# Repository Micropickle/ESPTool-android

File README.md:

# ESPTool-android
an extension to your phone meant to provide extended RF capabilities

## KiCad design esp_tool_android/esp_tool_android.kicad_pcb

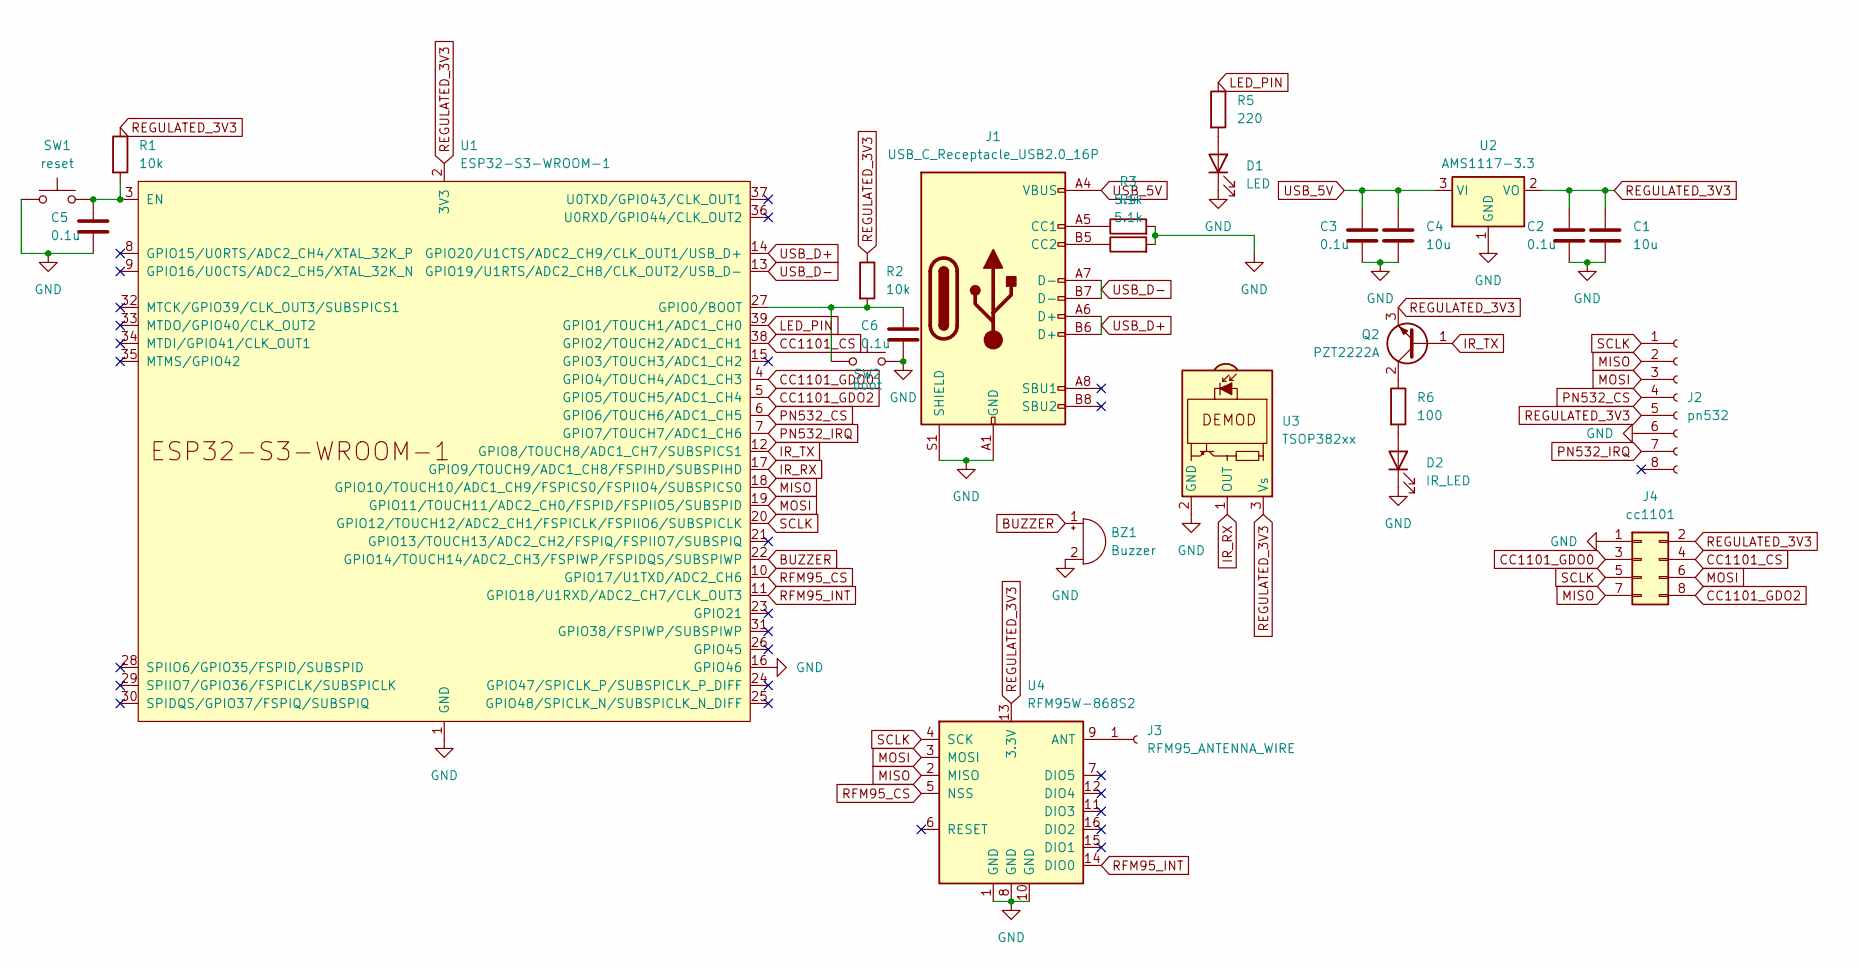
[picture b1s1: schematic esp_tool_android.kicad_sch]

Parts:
BZ1: Buzzer; PinHeader_1x02_P2.54mm_Vertical
C1, C4: 10u; C_0805_2012Metric
C2, C3, C5, C6: 0.1u; C_0805_2012Metric
D1: LED; LED_0805_2012Metric
D2: IR_LED; LED_D3.0mm_Horizontal_O1.27mm_Z2.0mm_Clear
J1: USB_C_Receptacle_USB2.0_16P; USB_C_Receptacle_HRO_TYPE-C-31-M-12
J2: pn532; PinHeader_1x08_P2.54mm_Vertical
J3: RFM95_ANTENNA_WIRE; PinHeader_1x01_P2.54mm_Vertical
J4: cc1101; PinHeader_2x04_P2.54mm_Vertical
Q2: PZT2222A; SOT-223-3_TabPin2
R1, R2: 10k; R_0805_2012Metric
R3, R4: 5.1k; R_0805_2012Metric
R5: 220; R_0805_2012Metric
R6: 100; R_0805_2012Metric
SW1: reset; SW_PUSH_6mm_H5mm
SW2: boot; SW_PUSH_6mm_H5mm
U1: ESP32-S3-WROOM-1
U2: AMS1117-3.3; SOT-223-3_TabPin2
U3: TSOP382xx; Vishay_MINICAST-3Pin
U4: RFM95W-868S2; HOPERF_RFM9XW_SMD

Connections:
BUZZER: BZ1.1 (+), U1.22 (GPIO14/TOUCH14/ADC2_CH3/FSPIWP/FSPIDQS/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)
CC1101_CS: J4.4, U1.38 (GPIO2/TOUCH2/ADC1_CH1)
CC1101_GDO0: J4.3, U1.4 (GPIO4/TOUCH4/ADC1_CH3)
CC1101_GDO2: J4.8, U1.5 (GPIO5/TOUCH5/ADC1_CH4)
GND: BZ1.2 (-), C1.2, C2.2, C3.2, C4.2, C5.2, C6.2, D1.1 (K), D2.1 (K), J1.A1 (GND), J1.A12 (GND), J1.B1 (GND), J1.B12 (GND), J1.S1 (SHIELD), J2.6, J4.1, R3.2, R4.2, SW1.1, SW2.2, U1.1 (GND), U1.16 (GPIO46), U1.40 (GND), U1.41 (GND), U2.1 (GND), U3.2 (GND), U4.1 (GND), U4.8 (GND), U4.10 (GND)
IR_RX: U1.17 (GPIO9/TOUCH9/ADC1_CH8/FSPIHD/SUBSPIHD), U3.1 (OUT)
IR_TX: Q2.1 (B), U1.12 (GPIO8/TOUCH8/ADC1_CH7/SUBSPICS1)
LED_PIN: R5.1, U1.39 (GPIO1/TOUCH1/ADC1_CH0)
MISO: J2.2, J4.7, U1.18 (GPIO10/TOUCH10/ADC1_CH9/FSPICS0/FSPIIO4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), U4.2 (MISO)
MOSI: J2.3, J4.6, U1.19 (GPIO11/TOUCH11/ADC2_CH0/FSPID/FSPIIO5/S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), U4.3 (MOSI)
unnamed: D1.2 (A), R5.2
unnamed: D2.2 (A), R6.2
unnamed: J1.A5 (CC1), R3.1
unnamed: J1.B5 (CC2), R4.1
unnamed: J3.1, U4.9 (ANT)
unnamed: Q2.2 (C), R6.1
unnamed: C5.1, R1.2, SW1.2, U1.3 (EN)
unnamed: C6.1, R2.2, SW2.1, U1.27 (GPIO0/BOOT)
PN532_CS: J2.4, U1.6 (GPIO6/TOUCH6/ADC1_CH5)
PN532_IRQ: J2.7, U1.7 (GPIO7/TOUCH7/ADC1_CH6)
REGULATED_3V3: C1.1, C2.1, J2.5, J4.2, Q2.3 (E), R1.1, R2.1, U1.2 (3V3), U2.2 (VO), U3.3 (Vs), U4.13 (3.3V)
RFM95_CS: U1.10 (GPIO17/U1TXD/ADC2_CH6), U4.5 (NSS)
RFM95_INT: U1.11 (GPIO18/U1RXD/ADC2_CH7/CLK_OUT3), U4.14 (DIO0)
SCLK: J2.1, J4.5, U1.20 (GPIO12/TOUCH12/ADC2_CH1/FSPICLK/FSPIIO6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), U4.4 (SCK)
USB_5V: C3.1, C4.1, J1.A4 (VBUS), J1.A9 (VBUS), J1.B4 (VBUS), J1.B9 (VBUS), U2.3 (VI)
USB_D+: J1.A6 (D+), J1.B6 (D+), U1.14 (GPIO20/U1CTS/ADC2_CH9/CLK_OUT1/USB_D+)
USB_D-: J1.A7 (D-), J1.B7 (D-), U1.13 (GPIO19/U1RTS/ADC2_CH8/CLK_OUT2/USB_D-)

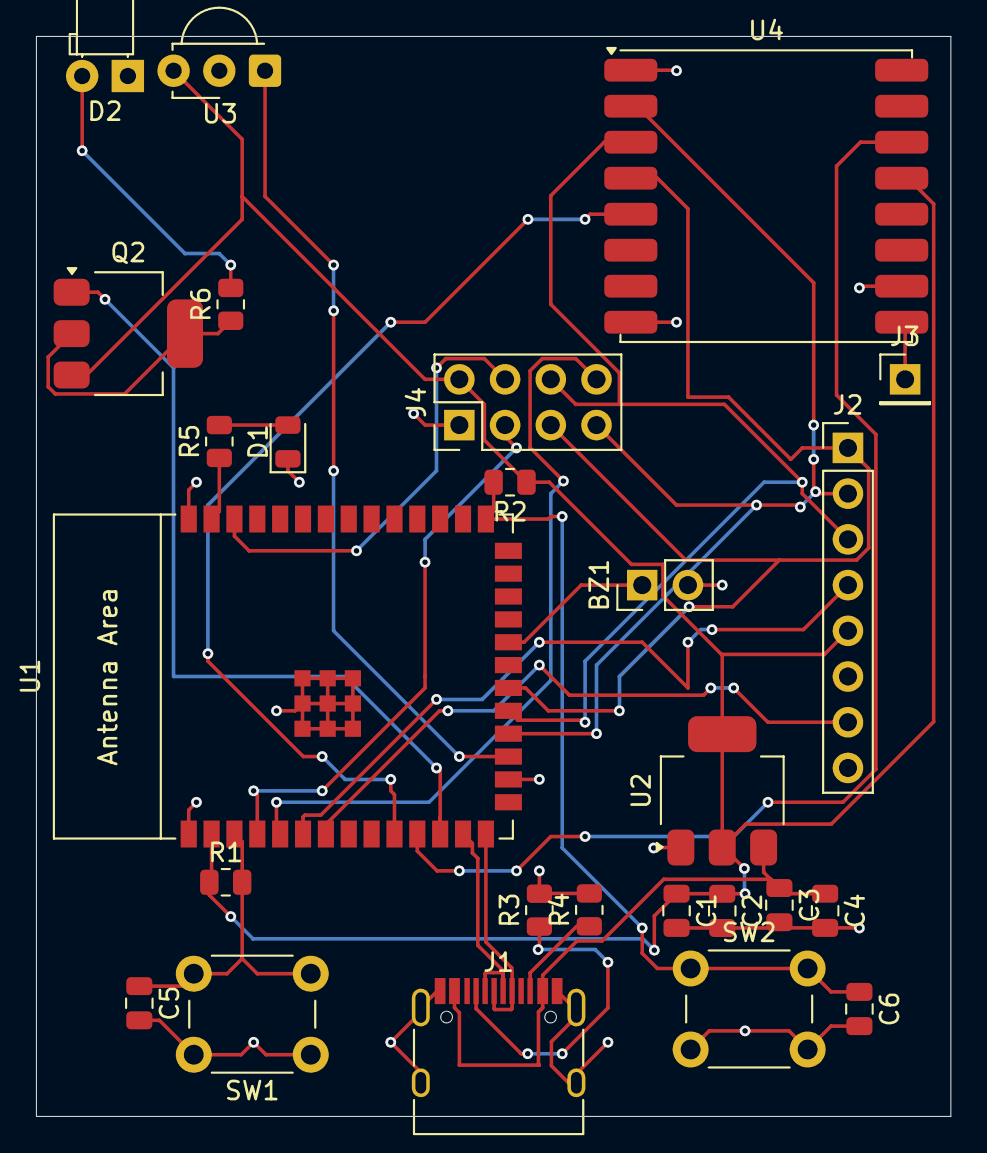
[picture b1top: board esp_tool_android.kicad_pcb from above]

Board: 2 copper layers, 50.8 x 60.0 mm, 26 parts (0 on the bottom side), 27 nets.

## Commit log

2025-12-14 Initialize README with project details
    Add project title and description to README
2025-12-16 Add .gitignore for KiCad project files
